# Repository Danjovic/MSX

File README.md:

# MSX
Coletânea de projetos para MSX

1) - Cartucho Caps Lock para Expert, descrito em http://danjovic.blogspot.com/2016/10/cartucho-caps-lock-para-expert.html

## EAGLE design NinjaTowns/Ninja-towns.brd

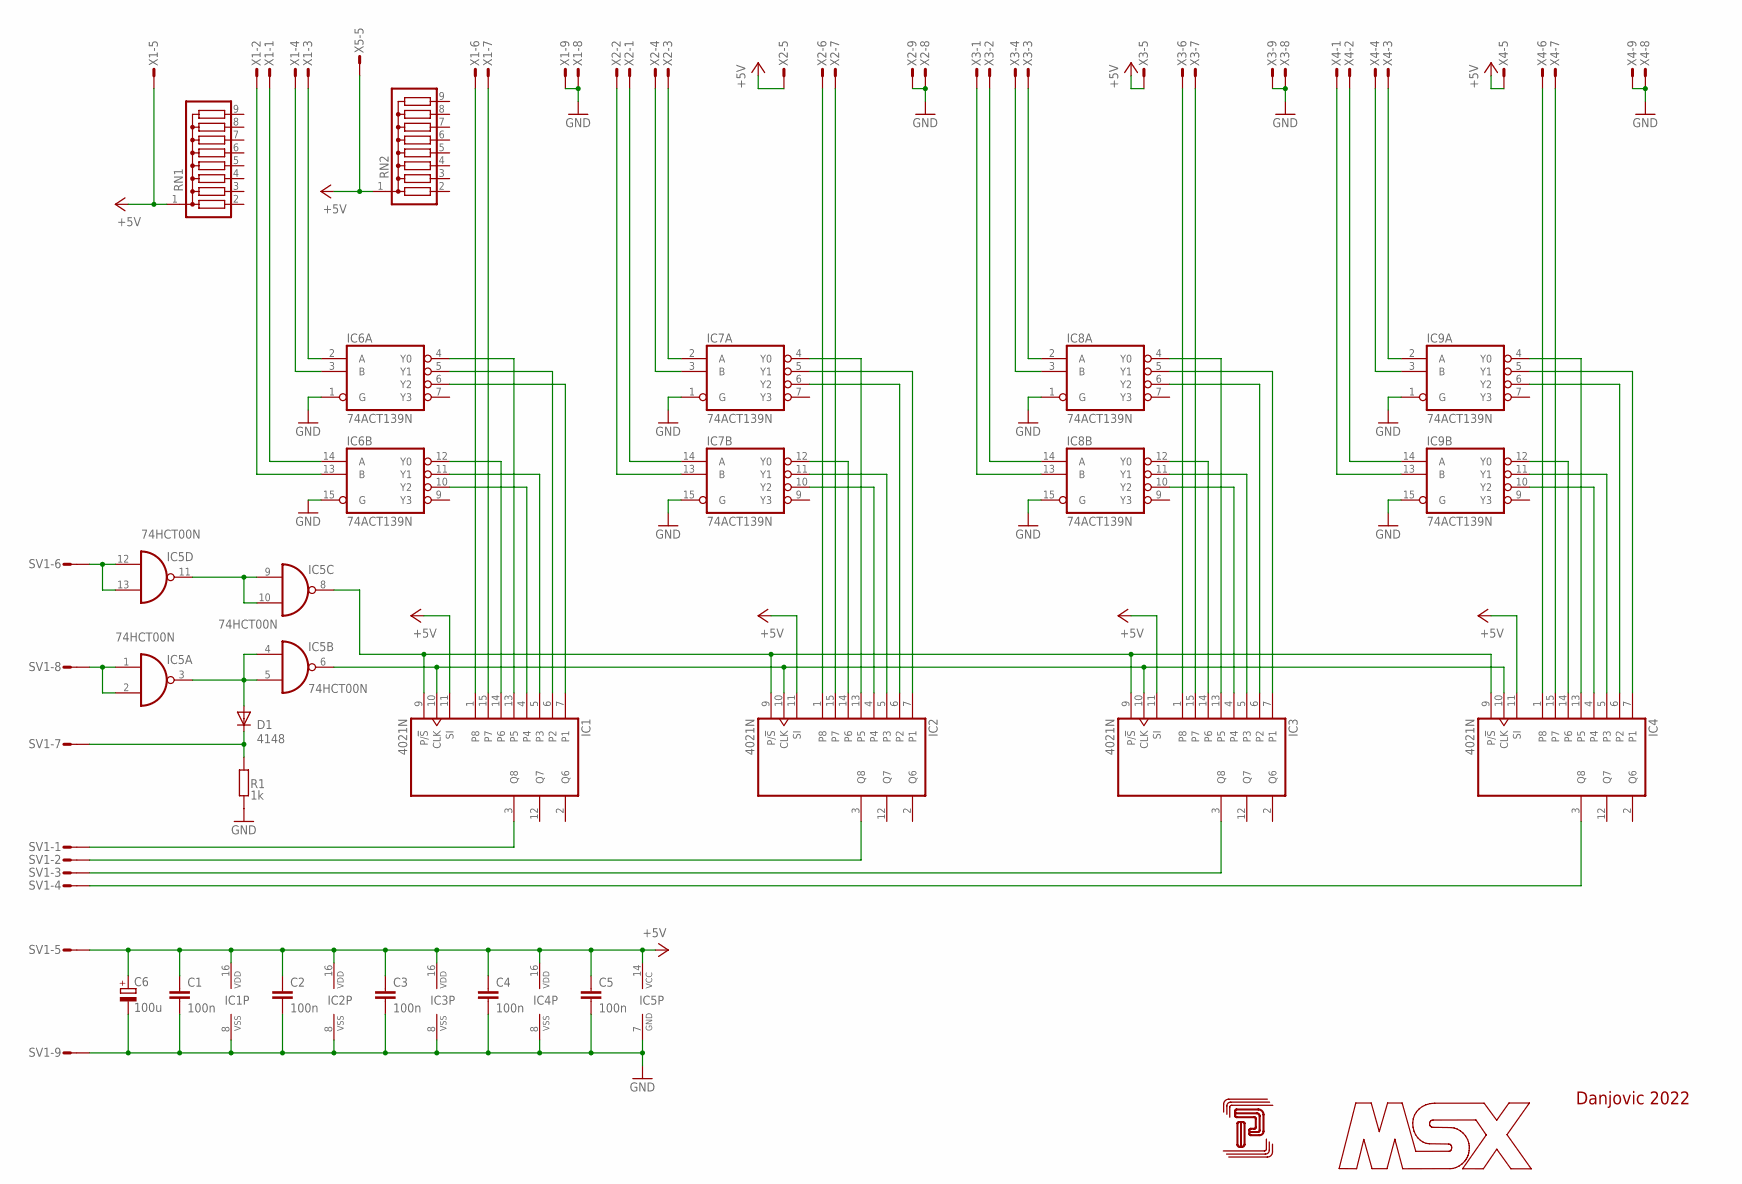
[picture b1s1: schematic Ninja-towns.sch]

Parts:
C1, C2, C3, C4, C5: 100n; C050-024X044
C6: 100u; E2,5-6
D1: 4148; D-5
IC1, IC2, IC3, IC4: 4021N; DIL16
IC5: 74HCT00N; DIL14
IC6, IC7, IC8, IC9: 74ACT139N; DIL16
R1: 1k; 0204/7L
RN1, RN2: G08R; SIL9
SV1: S09P
U$1: PB-202_TOP; PB202-TOP
X1, X2, X3, X4, X5: M09-182S; 182-009-MALE

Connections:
+5V: C1.1, C2.1, C3.1, C4.1, C5.1, C6.+, IC1.11 (SI), IC1.16 (VDD), IC2.11 (SI), IC2.16 (VDD), IC3.11 (SI), IC3.16 (VDD), IC4.11 (SI), IC4.16 (VDD), IC5.14 (VCC), RN1.1, RN2.1, SV1.5, X1.5, X2.5, X3.5, X4.5, X5.5
GND: C1.2, C2.2, C3.2, C4.2, C5.2, C6.-, IC1.8 (VSS), IC2.8 (VSS), IC3.8 (VSS), IC4.8 (VSS), IC5.7 (GND), IC6.1 (G), IC6.8 (GND), IC6.15 (G), IC7.1 (G), IC7.8 (GND), IC7.15 (G), IC8.1 (G), IC8.8 (GND), IC8.15 (G), IC9.1 (G), IC9.8 (GND), IC9.15 (G), R1.1, SV1.9, X1.8, X1.9, X2.8, X2.9, X3.8, X3.9, X4.8, X4.9
unnamed: IC1.3 (Q8), SV1.1
unnamed: IC2.3 (Q8), SV1.2
unnamed: IC3.3 (Q8), SV1.3
unnamed: IC4.3 (Q8), SV1.4
unnamed: D1.A, IC5.3 (O), IC5.4 (I0), IC5.5 (I1)
unnamed: IC1.10 (CLK), IC2.10 (CLK), IC3.10 (CLK), IC4.10 (CLK), IC5.6 (O)
unnamed: IC1.1 (P8), X1.6
unnamed: IC1.15 (P7), X1.7
unnamed: IC1.14 (P6), IC6.12 (Y0)
unnamed: IC1.13 (P5), IC6.4 (Y0)
unnamed: IC1.4, IC6.10 (Y2)
unnamed: IC1.5 (P3), IC6.11 (Y1)
unnamed: IC1.6 (P2), IC6.5 (Y1)
unnamed: IC1.7 (P1), IC6.6 (Y2)
unnamed: IC2.1 (P8), X2.6
unnamed: IC2.15 (P7), X2.7
unnamed: IC2.14 (P6), IC7.12 (Y0)
unnamed: IC2.13 (P5), IC7.4 (Y0)
unnamed: IC2.4, IC7.10 (Y2)
unnamed: IC2.5 (P3), IC7.11 (Y1)
unnamed: IC2.6 (P2), IC7.6 (Y2)
unnamed: IC2.7 (P1), IC7.5 (Y1)
unnamed: IC3.1 (P8), X3.6
unnamed: IC3.15 (P7), X3.7
unnamed: IC3.14 (P6), IC8.12 (Y0)
unnamed: IC3.13 (P5), IC8.4 (Y0)
unnamed: IC3.4, IC8.10 (Y2)
unnamed: IC3.5 (P3), IC8.11 (Y1)
unnamed: IC3.6 (P2), IC8.6 (Y2)
unnamed: IC3.7 (P1), IC8.5 (Y1)
unnamed: IC4.1 (P8), X4.6
unnamed: IC4.15 (P7), X4.7
unnamed: IC4.14 (P6), IC9.12 (Y0)
unnamed: IC4.13 (P5), IC9.4 (Y0)
unnamed: IC4.4, IC9.10 (Y2)
unnamed: IC4.5 (P3), IC9.11 (Y1)
unnamed: IC4.6 (P2), IC9.6 (Y2)
unnamed: IC4.7 (P1), IC9.5 (Y1)
unnamed: IC5.9 (I0), IC5.10 (I1), IC5.11 (O)
unnamed: IC6.2 (A), X1.3
unnamed: IC1.9 (P/!S), IC2.9 (P/!S), IC3.9 (P/!S), IC4.9 (P/!S), IC5.8 (O)
unnamed: IC5.12 (I0), IC5.13 (I1), SV1.6
unnamed: IC5.1 (I0), IC5.2 (I1), SV1.8
unnamed: D1.C, R1.2, SV1.7
unnamed: IC6.3 (B), X1.4
unnamed: IC6.14 (A), X1.1
unnamed: IC6.13 (B), X1.2
unnamed: IC7.2 (A), X2.3
unnamed: IC7.3 (B), X2.4
unnamed: IC7.14 (A), X2.1
unnamed: IC7.13 (B), X2.2
unnamed: IC8.2 (A), X3.3
unnamed: IC8.3 (B), X3.4
unnamed: IC9.2 (A), X4.3
unnamed: IC8.14 (A), X3.2
unnamed: IC8.13 (B), X3.1
unnamed: IC9.3 (B), X4.4
unnamed: IC9.14 (A), X4.2
unnamed: IC9.13 (B), X4.1
VCC: IC6.16 (VCC), IC7.16 (VCC), IC8.16 (VCC), IC9.16 (VCC)

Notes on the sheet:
Danjovic 2022

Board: 2 copper layers, 26 parts (0 on the bottom side), 62 nets, no tracks yet.

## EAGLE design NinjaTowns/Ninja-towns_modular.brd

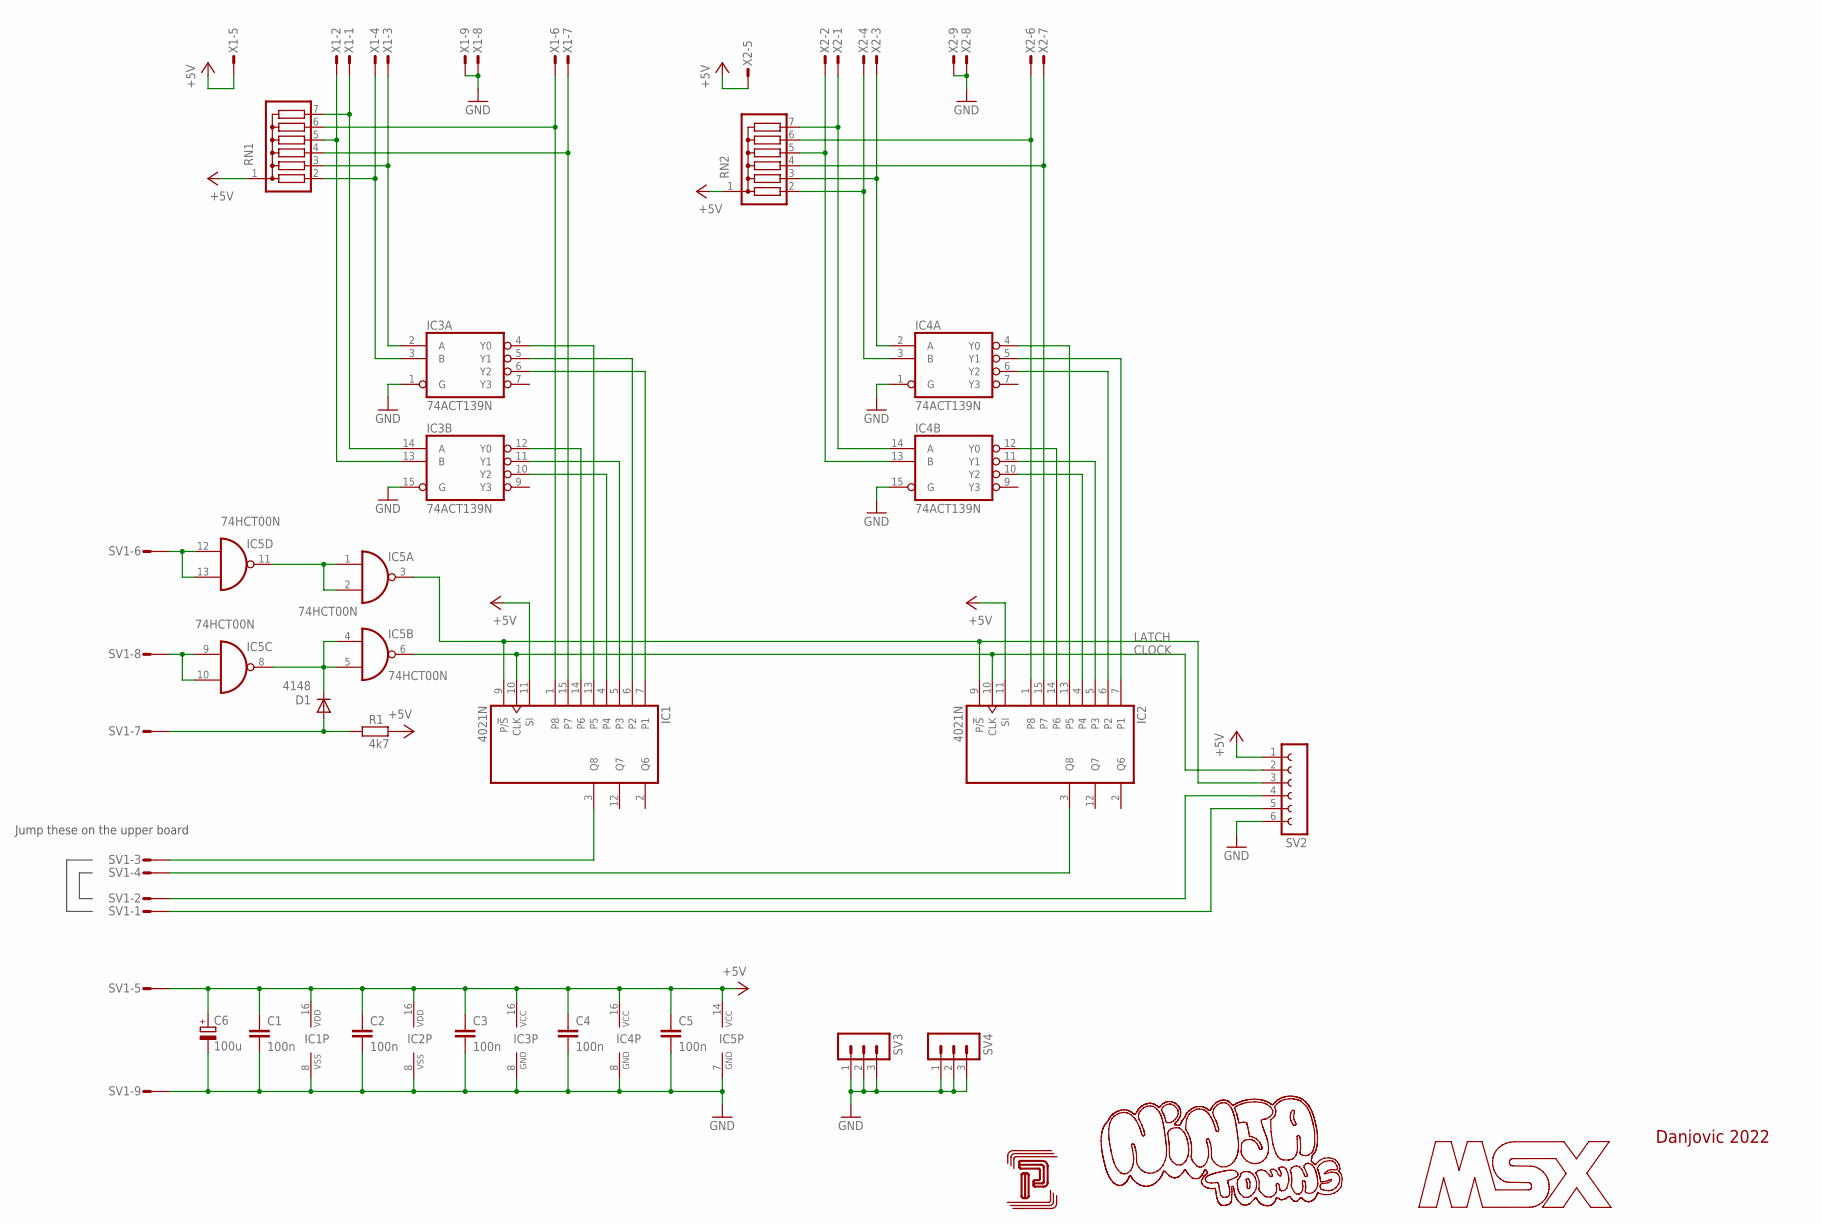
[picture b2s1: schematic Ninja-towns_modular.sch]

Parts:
C1, C2, C3, C4, C5: 100n; C050-024X044
C6: 100u; E2,5-6
D1: 4148; D-5
IC1, IC2: 4021N; DIL16
IC3, IC4: 74ACT139N; DIL16
IC5: 74HCT00N; DIL14
R1: 4k7; 0204/7L
RN1, RN2: G06R; SIL7
SV1: S09P
SV2: FE06-1; FE06
SV3, SV4: MA03-1
U$1: PB-203_TOP; PB203-TOP
X1, X2: M09-182S; 182-009-MALE

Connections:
+5V: C1.1, C2.1, C3.1, C4.1, C5.1, C6.+, IC1.11 (SI), IC1.16 (VDD), IC2.11 (SI), IC2.16 (VDD), IC3.16 (VCC), IC4.16 (VCC), IC5.14 (VCC), R1.1, RN1.1, RN2.1, SV1.5, SV2.1, X1.5, X2.5
CLOCK: IC1.10 (CLK), IC2.10 (CLK), IC5.6 (O), SV2.2
GND: C1.2, C2.2, C3.2, C4.2, C5.2, C6.-, IC1.8 (VSS), IC2.8 (VSS), IC3.1 (G), IC3.8 (GND), IC3.15 (G), IC4.1 (G), IC4.8 (GND), IC4.15 (G), IC5.7 (GND), SV1.9, SV2.6, SV3.1, SV3.2, SV3.3, SV4.1, SV4.2, SV4.3, X1.8, X1.9, X2.8, X2.9
LATCH: IC1.9 (P/!S), IC2.9 (P/!S), IC5.3 (O), SV2.3
unnamed: IC1.3 (Q8), SV1.3
unnamed: IC2.3 (Q8), SV1.4
unnamed: SV1.2, SV2.4
unnamed: SV1.1, SV2.5
unnamed: D1.C, IC5.4 (I0), IC5.5 (I1), IC5.8 (O)
unnamed: IC1.1 (P8), RN1.6, X1.6
unnamed: IC1.15 (P7), RN1.4, X1.7
unnamed: IC1.14 (P6), IC3.12 (Y0)
unnamed: IC1.13 (P5), IC3.4 (Y0)
unnamed: IC1.4, IC3.10 (Y2)
unnamed: IC1.5 (P3), IC3.11 (Y1)
unnamed: IC1.6 (P2), IC3.5 (Y1)
unnamed: IC1.7 (P1), IC3.6 (Y2)
unnamed: IC2.1 (P8), RN2.6, X2.6
unnamed: IC2.15 (P7), RN2.4, X2.7
unnamed: IC2.14 (P6), IC4.12 (Y0)
unnamed: IC2.13 (P5), IC4.4 (Y0)
unnamed: IC2.4, IC4.10 (Y2)
unnamed: IC2.5 (P3), IC4.11 (Y1)
unnamed: IC2.6 (P2), IC4.6 (Y2)
unnamed: IC2.7 (P1), IC4.5 (Y1)
unnamed: IC5.1 (I0), IC5.2 (I1), IC5.11 (O)
unnamed: IC3.2 (A), RN1.3, X1.3
unnamed: IC5.12 (I0), IC5.13 (I1), SV1.6
unnamed: IC5.9 (I0), IC5.10 (I1), SV1.8
unnamed: D1.A, R1.2, SV1.7
unnamed: IC3.3 (B), RN1.2, X1.4
unnamed: IC3.14 (A), RN1.7, X1.1
unnamed: IC3.13 (B), RN1.5, X1.2
unnamed: IC4.2 (A), RN2.3, X2.3
unnamed: IC4.3 (B), RN2.2, X2.4
unnamed: IC4.14 (A), RN2.7, X2.1
unnamed: IC4.13 (B), RN2.5, X2.2

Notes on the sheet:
Danjovic 2022
Jump these on the upper board

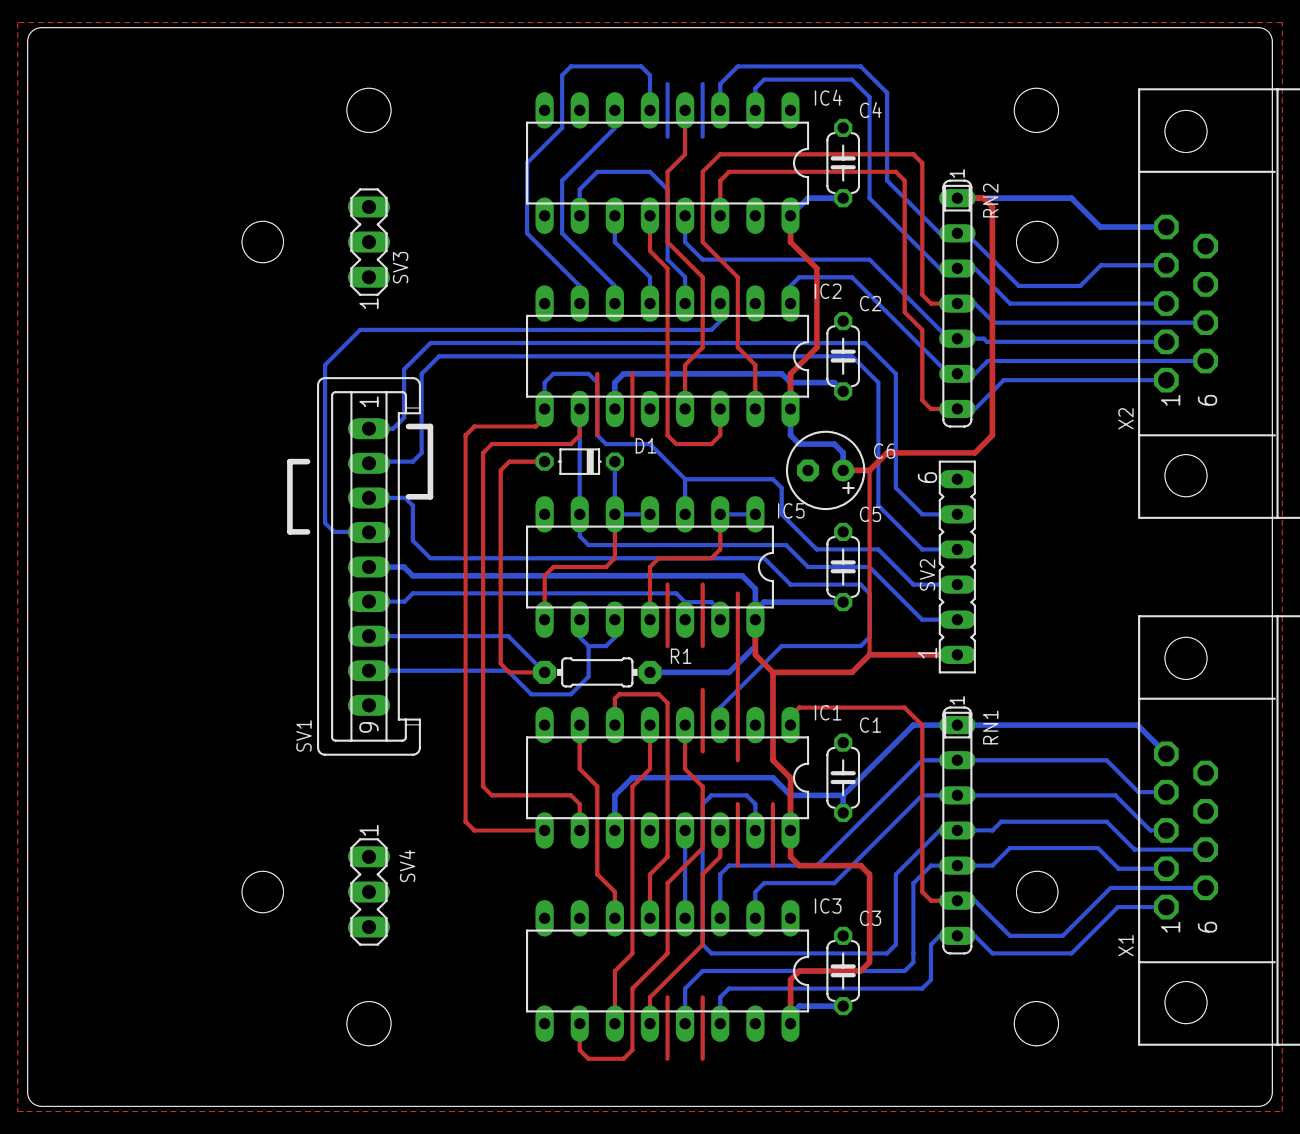
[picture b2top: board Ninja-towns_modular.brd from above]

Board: 2 copper layers, 90.0 x 78.0 mm, 22 parts (0 on the bottom side), 37 nets.

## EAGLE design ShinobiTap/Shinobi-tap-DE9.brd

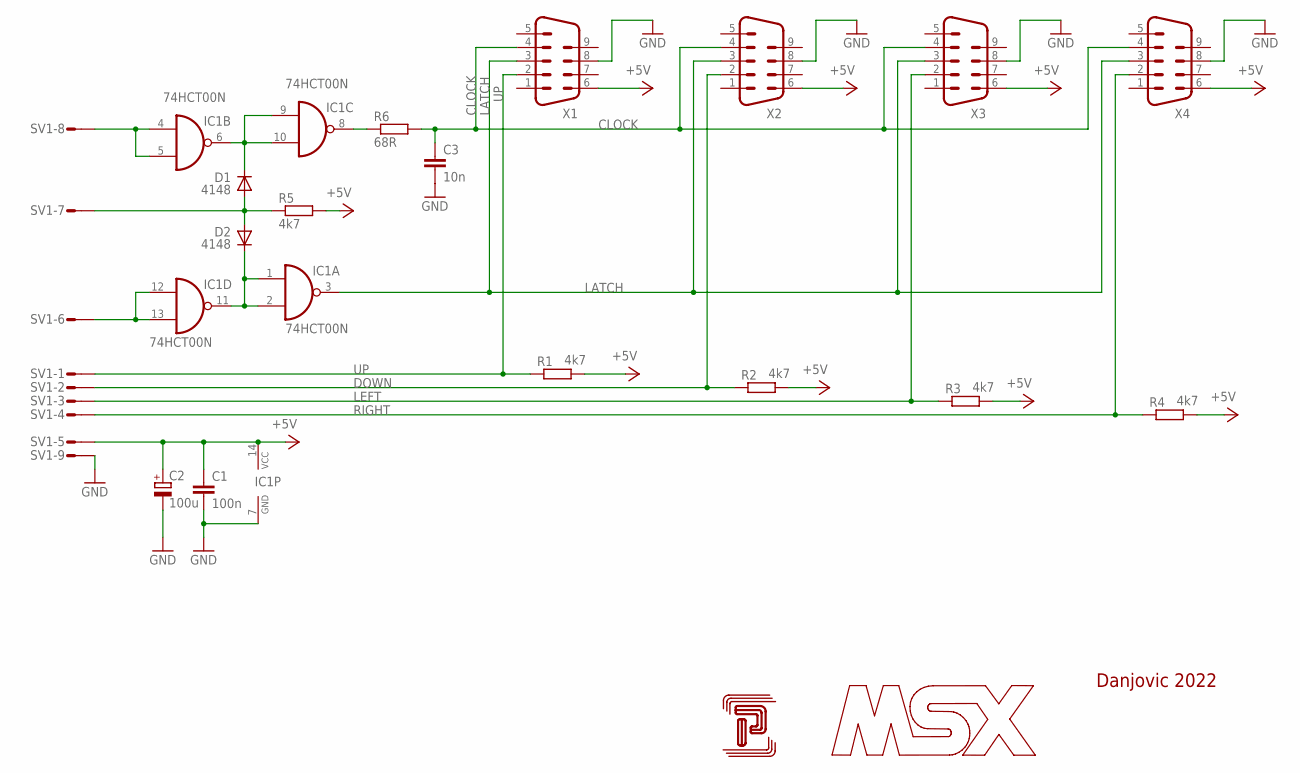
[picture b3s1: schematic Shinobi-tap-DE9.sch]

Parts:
C1: 100n; C050-024X044L
C2: 100u; E2,5-6
C3: 10n; C050-024X044L
D1, D2: 4148; D-7.5
IC1: 74HCT00N; DIL14
R1, R2, R3, R4, R5: 4k7; 0204/7L
R6: 68R; 0204/7L
SV1: S09P
U$1: CP-011
X1, X2, X3, X4: M09-182; 182-009-MALE

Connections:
+5V: C1.1, C2.+, IC1.14 (VCC), R1.2, R2.2, R3.2, R4.2, R5.2, SV1.5, X1.6, X2.6, X3.6, X4.6
CLOCK: C3.1, R6.2, X1.4, X2.4, X3.4, X4.4
DOWN: R2.1, SV1.2, X2.2
GND: C1.2, C2.-, C3.2, IC1.7 (GND), SV1.9, X1.8, X2.8, X3.8, X4.8
LATCH: IC1.3 (O), X1.3, X2.3, X3.3, X4.3
LEFT: R3.1, SV1.3, X3.2
unnamed: IC1.8 (O), R6.1
unnamed: D2.C, IC1.1 (I0), IC1.2 (I1), IC1.11 (O)
unnamed: D1.C, IC1.6 (O), IC1.9 (I0), IC1.10 (I1)
PULSE: IC1.4 (I0), IC1.5 (I1), SV1.8
RIGHT: R4.1, SV1.4, X4.2
TRGA: IC1.12 (I0), IC1.13 (I1), SV1.6
TRGB: D1.A, D2.A, R5.1, SV1.7
UP: R1.1, SV1.1, X1.2

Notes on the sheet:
Danjovic 2022

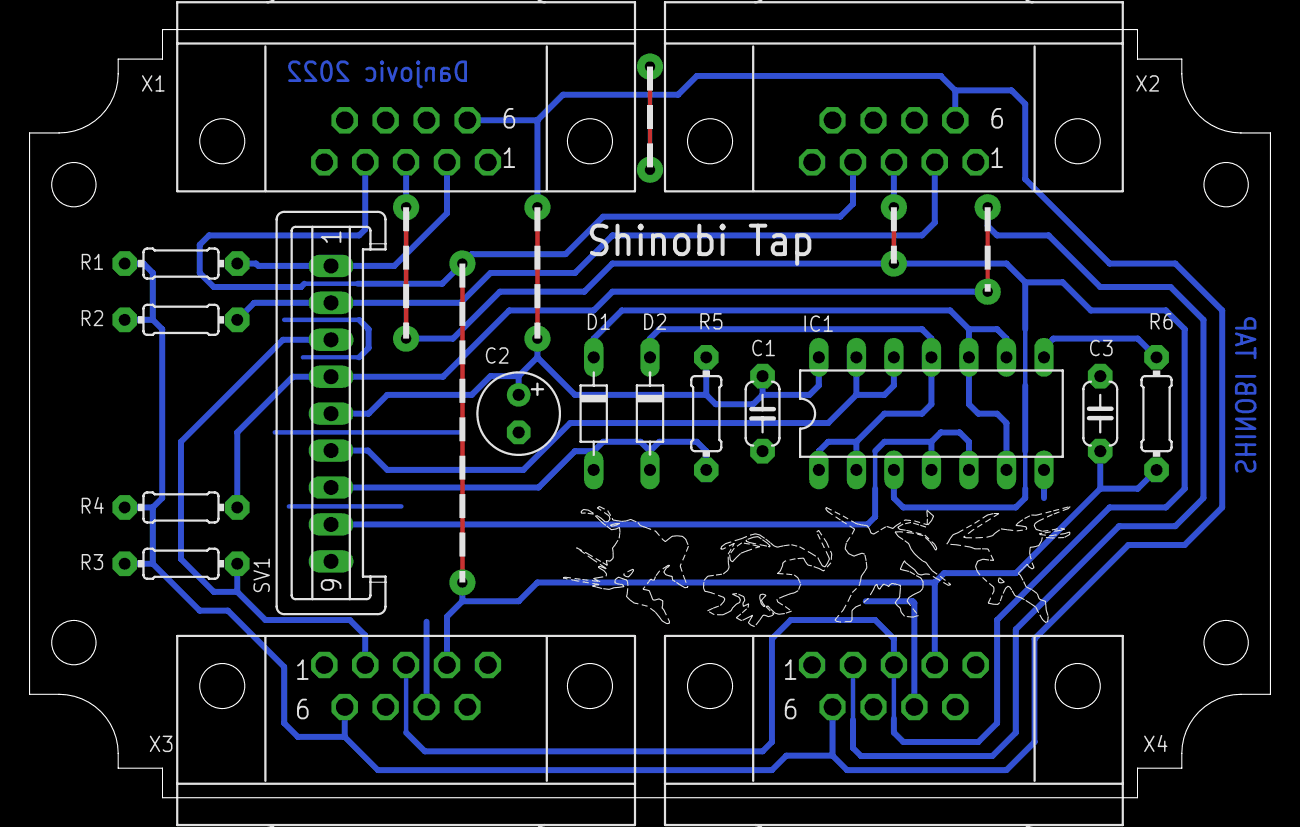
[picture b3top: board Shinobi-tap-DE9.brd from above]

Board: 2 copper layers, 84.0 x 52.0 mm, 18 parts (0 on the bottom side), 14 nets.

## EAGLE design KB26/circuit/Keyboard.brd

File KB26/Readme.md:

# Atari keyboard controller Adapter # 
Atari keybads are a 3x4 matrix that can be read by MSX by pulling down consecutively the pins 6, 7, 8 to select the rows while the colums are read on the pins 1, 2, 3, 4. 

Pins 6 and 7 are native Open Collector In/Outs, while pin 8 is turned into an open collector by a 1n4148 diode and a 4k7 pullup resitor. 

## Schematics ##

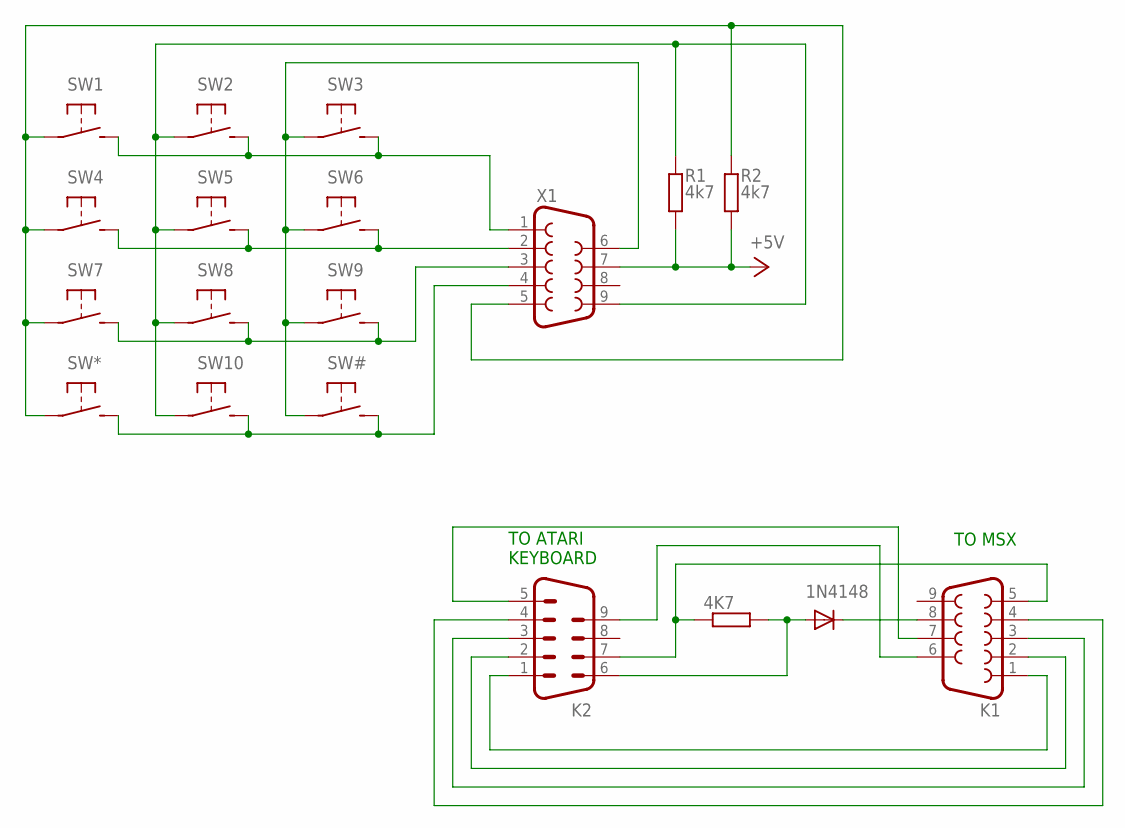
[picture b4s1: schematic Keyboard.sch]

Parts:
1N4148: DIODE-D-5; D-5
4K7: R-EU_0204/5; 0204/5
K1: F09D
K2: M09D
R1, R2: 4k7; 0204/7
SW1, SW2, SW3, SW4, SW5, SW6, SW7, SW8, SW9, SW10: MINISPDT; 2PST_MINI
SW#: MINISPDT; 2PST_MINI
SW*: MINISPDT; 2PST_MINI
X1: F09D

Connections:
+5V: R1.2, R2.2, X1.7
unnamed: SW1.P$2 (S), SW2.P$2 (S), SW3.P$2 (S), X1.1
unnamed: SW4.P$2 (S), SW5.P$2 (S), SW6.P$2 (S), X1.2
unnamed: SW7.P$2 (S), SW8.P$2 (S), SW9.P$2 (S), X1.3
unnamed: SW10.P$2 (S), SW#.P$2 (S), SW*.P$2 (S), X1.4
unnamed: SW3.P$1, SW6.P$1, SW9.P$1, SW#.P$1, X1.6
unnamed: R1.1, SW2.P$1, SW5.P$1, SW8.P$1, SW10.P$1, X1.9
unnamed: R2.1, SW1.P$1, SW4.P$1, SW7.P$1, SW*.P$1, X1.5
unnamed: 4K7.1, K1.5, K2.7
unnamed: 1N4148.C, K1.8
unnamed: K1.6, K2.9
unnamed: K1.7, K2.5
unnamed: K1.1, K2.1
unnamed: K1.2, K2.2
unnamed: 1N4148.A, 4K7.2, K2.6
unnamed: K1.3, K2.3
unnamed: K1.4, K2.4

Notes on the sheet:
TO ATARI KEYBOARD
TO MSX

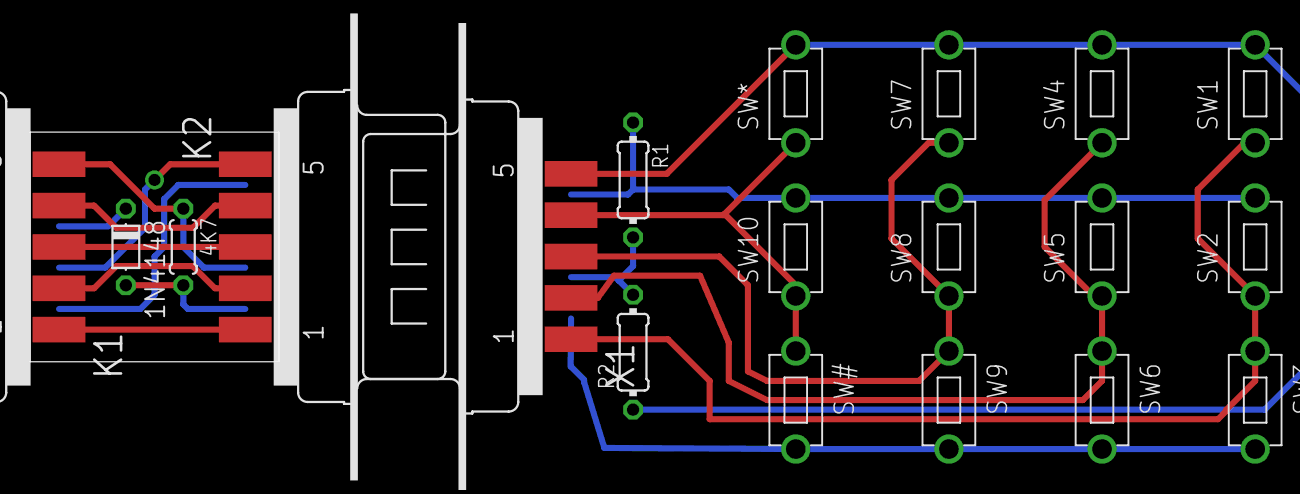
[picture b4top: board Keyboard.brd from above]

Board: 2 copper layers, 16.5 x 15.2 mm, 19 parts (0 on the bottom side), 17 nets.

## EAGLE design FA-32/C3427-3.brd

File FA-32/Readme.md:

# FA-32BR

Recreation of the FA-32 cassete recorder interface for the Casio MX-10, MX-101 and PV-7. 

The whole project was designed to be easy to reproduce. The original circuit was reverse engineered and a custom, 
single sided PCB was designed to fit into a [Hammond 1593J](http://www.hammondmfg.com/pdf/1593J.pdf) plastic case. 

The board provides options for some of the components:
- Relay:

  Original FBR211 series or a generic DPDT subminiature type with DIP spacing that can be found under several brands and part numbers

- Transistor

  Original 2SC945 [BCE] or a BC338 [EBC]

- EAR/MIC Input Jacks

  Two Mono Jacks PJ-301 or a Stereo Jack type PJ-325

The connection from the MSX to the board is done using a DIN-5 to DB-9 cable with the following wiring:

The connection to the Cassete depends upon the option used for the MIC/EAR jack:

- Two Mono Jacks PJ-301

- One Stereo Jack type PJ-325

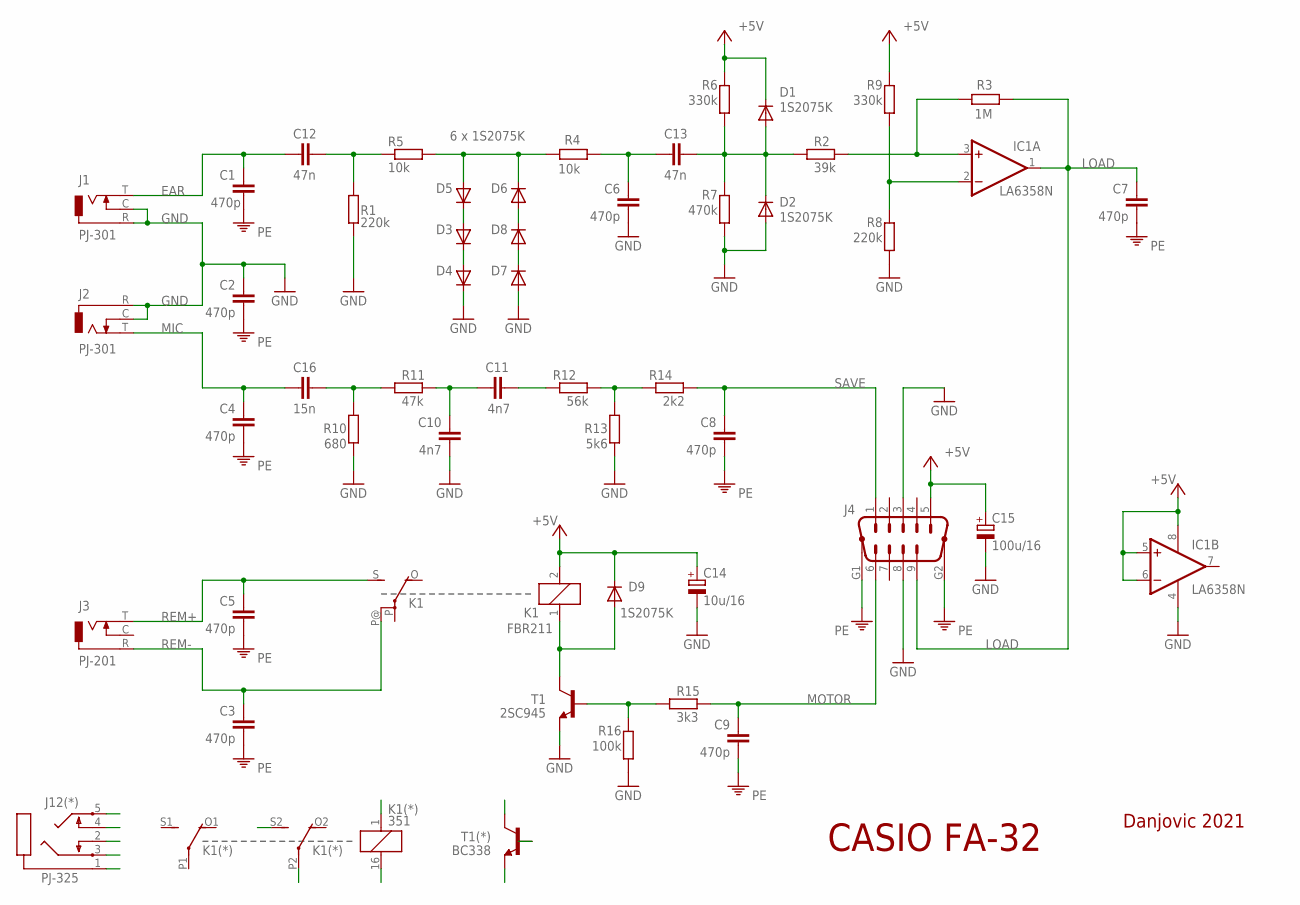
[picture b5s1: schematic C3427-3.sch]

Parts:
C1, C2, C3, C4, C5, C6, C7, C8, C9: 470p; C050-024X044
C10, C11: 4n7; C050-024X044
C12, C13: 47n; C050-045X075
C14: 10u/16; E2-4
C15: 100u/16; E2,5-6
C16: 15n; C050-024X044
D1, D2, D3, D4, D5, D6, D7, D8, D9: 1S2075K; D-7.5
IC1: LA6358N; DIL08
J1, J2: PJ-301; PJ301
J3: PJ-201; PJ201
J4: M09HP
J12(*): PJ-325; PJ325
K1: FBR211; FRS1B
K1(*): 351
R1, R8: 220k; 0204/7
R2: 39k; 0204/7
R3: 1M; 0204/7
R4, R5: 10k; 0204/7
R6, R9: 330k; 0204/7
R7: 470k; 0204/7
R10: 680; 0204/7
R11: 47k; 0204/7
R12: 56k; 0204/7
R13: 5k6; 0204/7
R14: 2k2; 0204/7
R15: 3k3; 0204/7
R16: 100k; 0204/7
T1: 2SC945; TO92-ECB
T1(*): BC338; TO92-EBC

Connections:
+5V: C14.+, C15.+, D1.C, D9.C, IC1.5 (+IN), IC1.6 (-IN), IC1.8 (V+), J4.5, K1.2, K1(*).1, R6.1, R9.1
EAR: C1.2, C12.2, J1.T, J12(*).5
GND: C2.2, C6.1, C10.1, C14.-, C15.-, D2.A, D4.C, D7.A, IC1.4 (V-), J1.C, J1.R, J2.C, J2.R, J4.3, J4.8, J12(*).1, J12(*).2, J12(*).4, R1.1, R7.1, R8.1, R10.1, R13.2, R16.2, T1.E, T1(*).E
LOAD: C7.2, IC1.1 (OUT), J4.9, R3.1
MIC: C4.2, C16.2, J2.T, J12(*).3
MOTOR: C9.2, J4.6, R15.2
unnamed: D5.A, D6.C, R4.2, R5.2
unnamed: C12.1, R1.2, R5.1
unnamed: C6.2, C13.2, R4.1
unnamed: C16.1, R10.2, R11.1
unnamed: D9.A, K1.1, K1(*).16 (2), T1.C, T1(*).C
unnamed: R15.1, R16.1, T1.B, T1(*).B
unnamed: D3.A, D5.C
unnamed: D3.C, D4.A
unnamed: D6.A, D8.C
unnamed: D7.C, D8.A
unnamed: C13.1, D1.A, D2.C, R2.1, R6.2, R7.2
unnamed: R12.2, R13.1, R14.1
unnamed: C10.2, C11.1, R11.2
unnamed: C11.2, R12.1
unnamed: IC1.2 (-IN), R8.2, R9.2
unnamed: IC1.3 (+IN), R2.2, R3.2
PE: C1.1, C2.1, C3.1, C4.1, C5.1, C7.1, C8.1, C9.1, J4.G1, J4.G2
REM+: C5.2, J3.T, K1.S, K1(*).P2
REM-: C3.2, J3.R, K1.P@, K1(*).S2 (S)
SAVE: C8.2, J4.1, R14.2

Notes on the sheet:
6 x 1S2075K
Danjovic 2021
CASIO FA-32

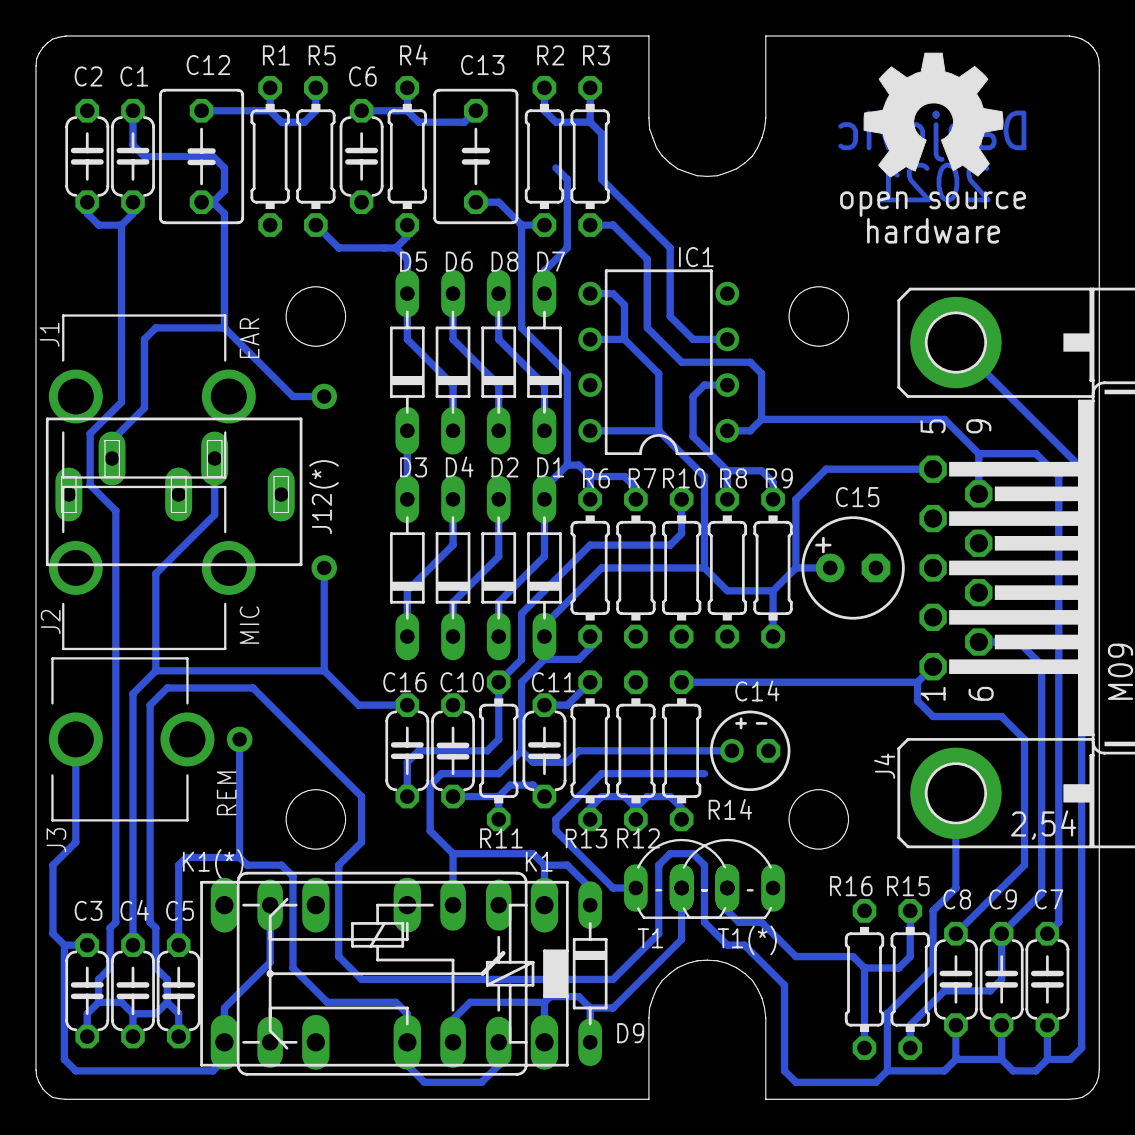
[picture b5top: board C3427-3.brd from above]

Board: 2 copper layers, 59.1 x 59.1 mm, 53 parts (0 on the bottom side), 26 nets.

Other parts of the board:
U$1: OSHW_8MM
U$2: 1593J

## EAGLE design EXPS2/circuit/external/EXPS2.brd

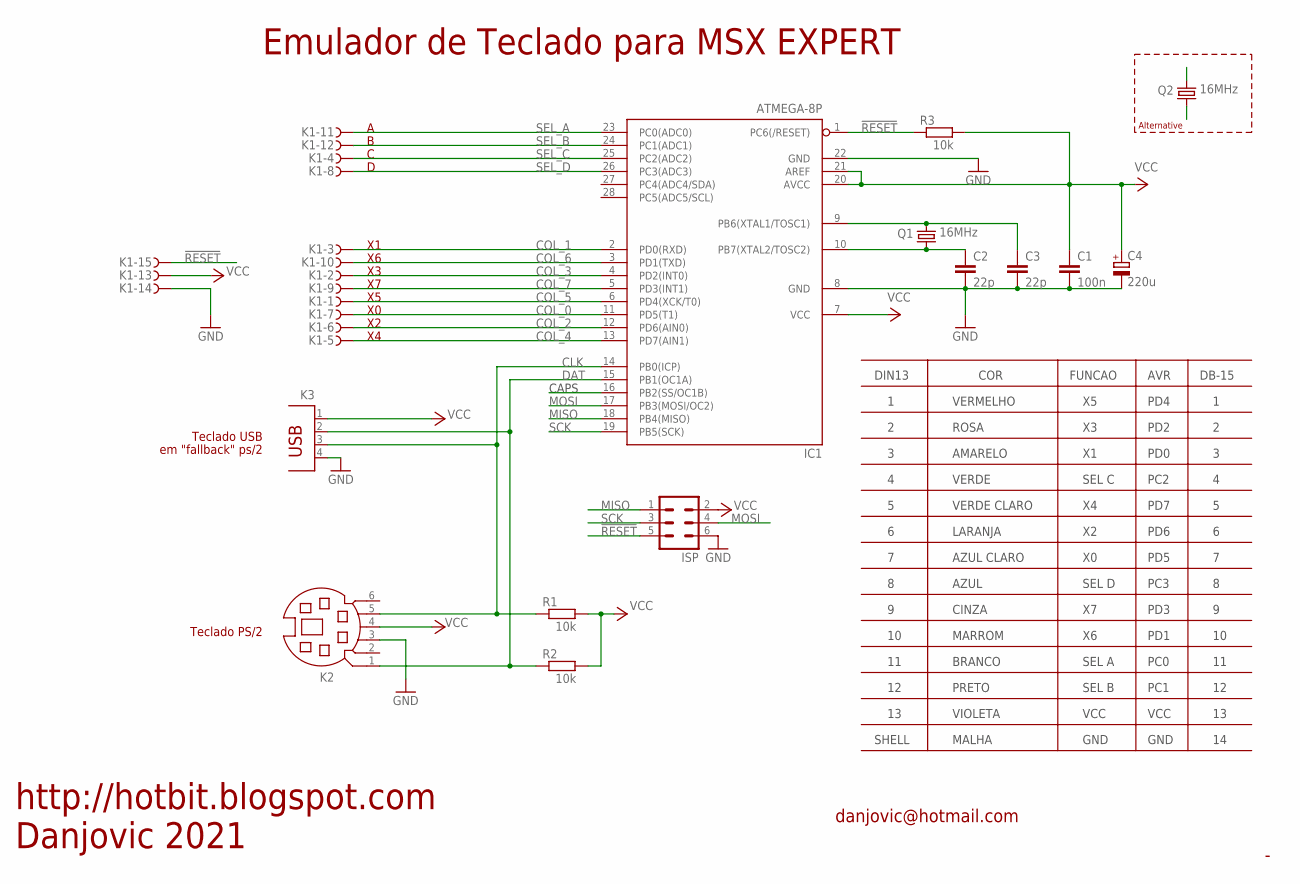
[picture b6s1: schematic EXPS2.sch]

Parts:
C1: 100n; C050-024X044
C2, C3: 22p; C050-024X044
C4: 220u; E2,5-6
IC1: ATMEGA-8P; DIL28-3
ISP: ML6
K1: F15HPS; F15HP
K2: MD06S; MDIN06S
K3: PN87520
Q1: 16MHz; HC49U-V
Q2: 16MHz; TC26H
R1, R2, R3: 10k; 0204/7

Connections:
!RESET: IC1.1 (PC6(/RESET)), ISP.5, K1.15, R3.2
CAPS: IC1.16 (PB2(SS/OC1B))
CLK: IC1.14 (PB0(ICP)), K2.5, K3.3, R1.1
COL_0: IC1.11 (PD5(T1)), K1.7
COL_1: IC1.2 (PD0(RXD)), K1.3
COL_2: IC1.12 (PD6(AIN0)), K1.6
COL_3: IC1.4 (PD2(INT0)), K1.2
COL_4: IC1.13 (PD7(AIN1)), K1.5
COL_5: IC1.6 (PD4(XCK/T0)), K1.1
COL_6: IC1.3 (PD1(TXD)), K1.10
COL_7: IC1.5 (PD3(INT1)), K1.9
DAT: IC1.15 (PB1(OC1A)), K2.1, K3.2, R2.1
GND: C1.2, C2.2, C3.2, C4.-, IC1.8 (GND), IC1.22 (GND), ISP.6, K1.14, K2.3, K3.4
MISO: IC1.18 (PB4(MISO)), ISP.1
MOSI: IC1.17 (PB3(MOSI/OC2)), ISP.4
SCK: IC1.19 (PB5(SCK)), ISP.3
SEL_A: IC1.23 (PC0(ADC0)), K1.11
SEL_B: IC1.24 (PC1(ADC1)), K1.12
SEL_C: IC1.25 (PC2(ADC2)), K1.4
SEL_D: IC1.26 (PC3(ADC3)), K1.8
VCC: C1.1, C4.+, IC1.7 (VCC), IC1.20 (AVCC), IC1.21 (AREF), ISP.2, K1.13, K2.4, K3.1, R1.2, R2.2, R3.1
XTAL1: C3.1, IC1.9 (PB6(XTAL1/TOSC1)), Q1.2, Q2.2
XTAL2: C2.1, IC1.10 (PB7(XTAL2/TOSC2)), Q1.1, Q2.1

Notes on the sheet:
Teclado PS/2
Emulador de Teclado para MSX EXPERT
Danjovic 2021
http://hotbit.blogspot.com
CAPS
danjovic@hotmail.com
Teclado USB
em "fallback" ps/2
DIN13
VERDE
VERDE CLARO
LARANJA
AZUL CLARO
AZUL
CINZA
MARROM
BRANCO
PRETO
VIOLETA
COR
AMARELO
ROSA
VERMELHO
SHELL
MALHA
SEL C
SEL D
SEL A
SEL B
VCC
FUNCAO
GND
PC2
PD7
PD6
PD5
PC3
PD3
PD1
PC0

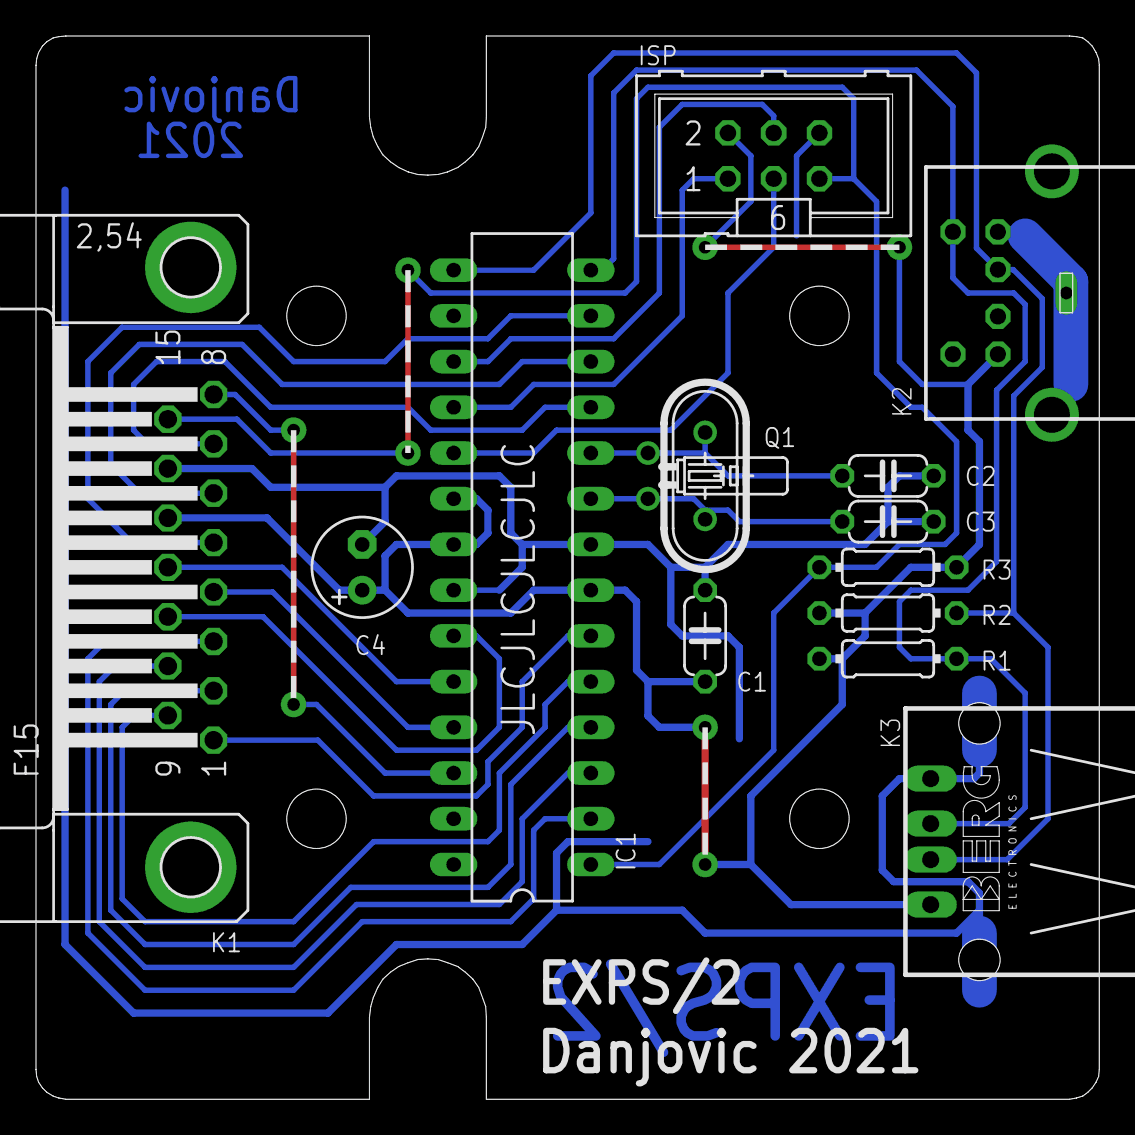
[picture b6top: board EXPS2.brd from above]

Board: 2 copper layers, 59.1 x 59.1 mm, 15 parts (0 on the bottom side), 22 nets.

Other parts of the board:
U$1: 1593J

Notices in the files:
Hydra/firmware/Hydra_sketch/Hydra_sketch.ino:
License:GPL V2.0
